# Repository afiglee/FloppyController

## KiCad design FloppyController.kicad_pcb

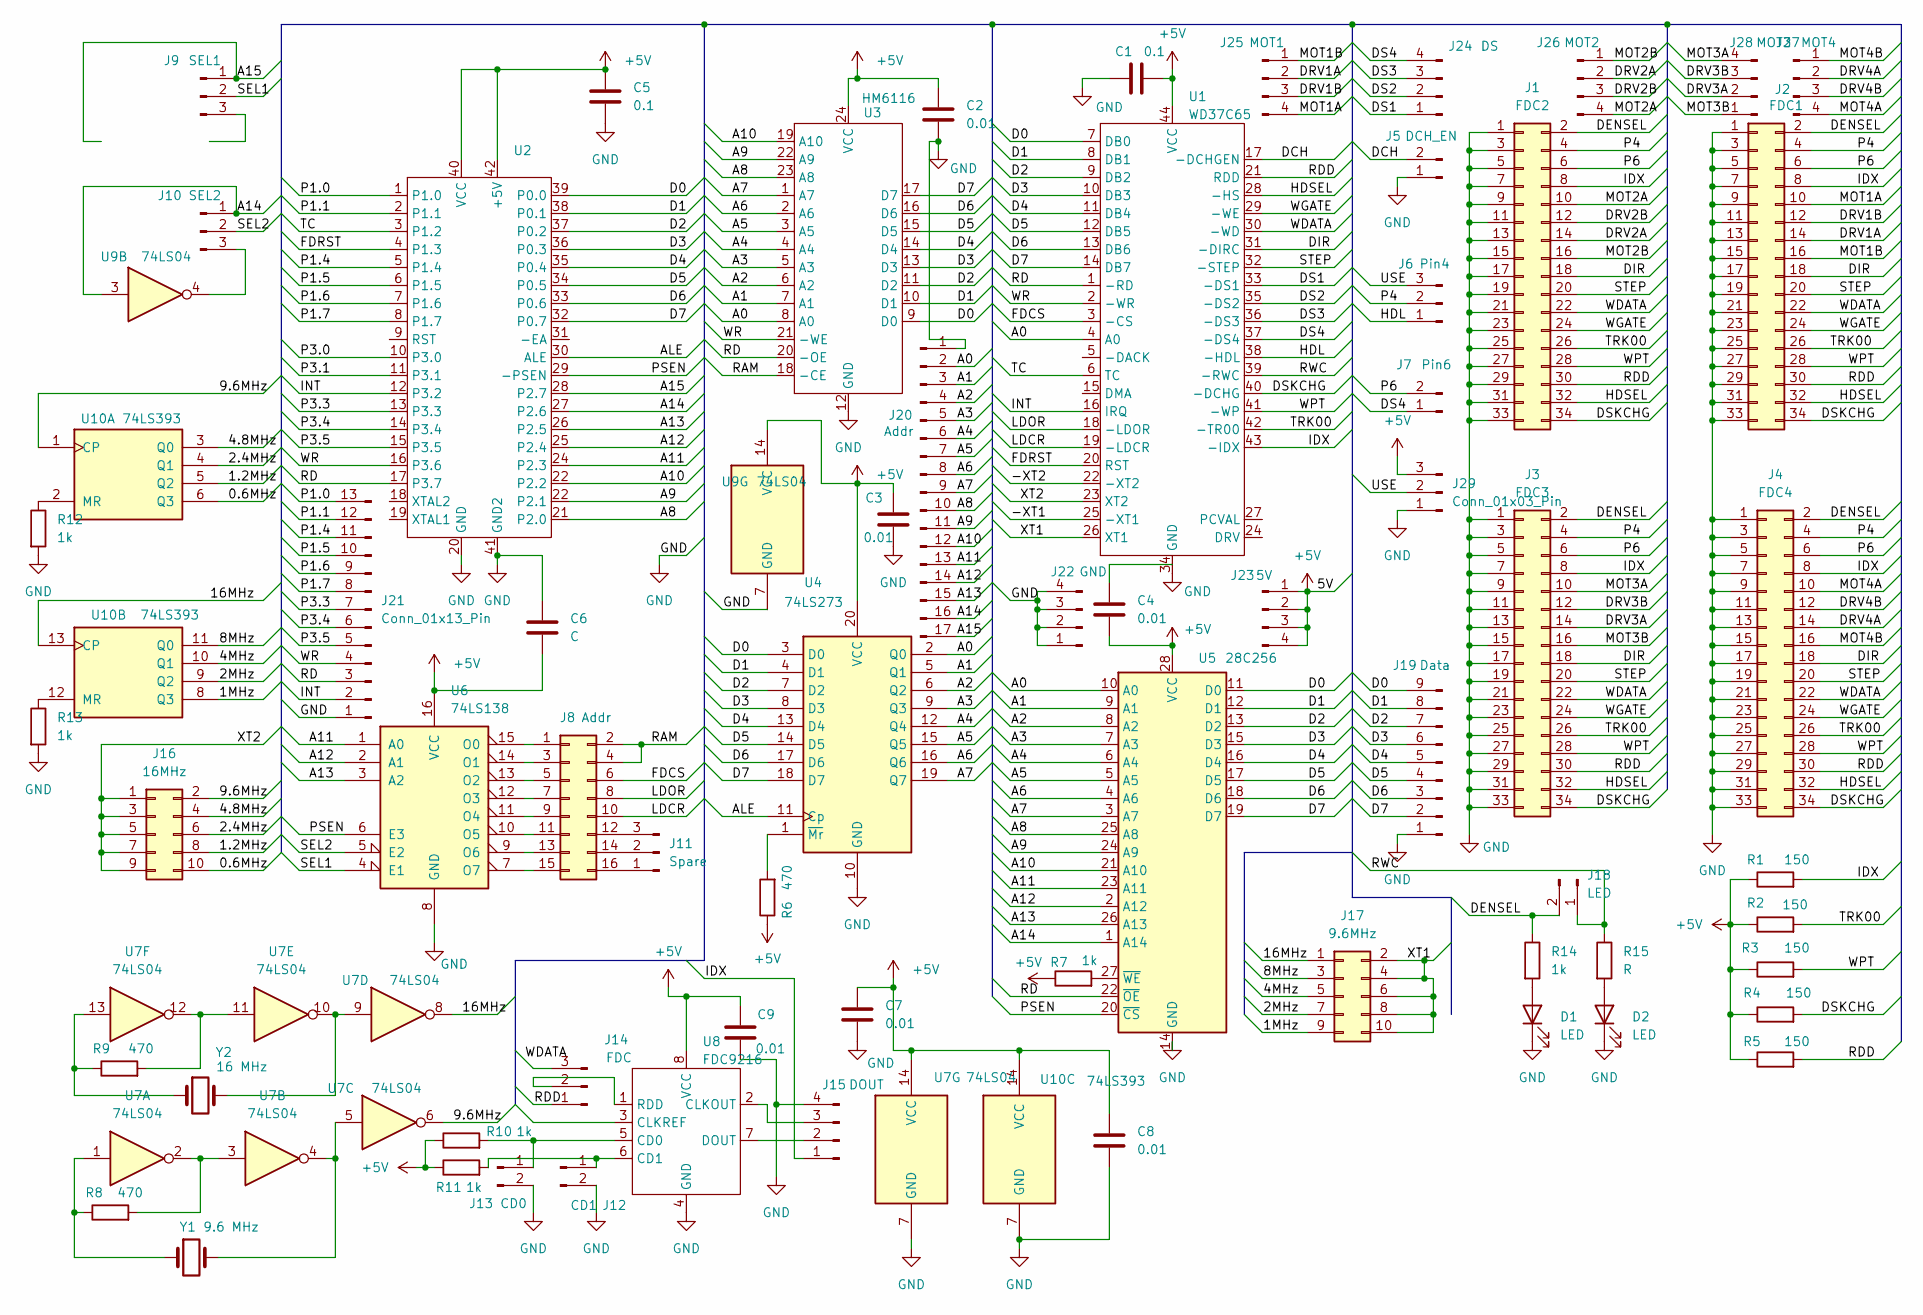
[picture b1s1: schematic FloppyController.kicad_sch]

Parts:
C1, C5: 0.1; C_Disc_D4.7mm_W2.5mm_P5.00mm
C2, C3, C4, C7, C8, C9: 0.01; C_Disc_D4.7mm_W2.5mm_P5.00mm
C6: C; C_Disc_D4.7mm_W2.5mm_P5.00mm
D1, D2: LED; LED_D5.0mm
J1: FDC2; PinHeader_2x17_P2.54mm_Vertical
J2: FDC1; PinHeader_2x17_P2.54mm_Vertical
J3: FDC3; PinHeader_2x17_P2.54mm_Vertical
J4: FDC4; PinHeader_2x17_P2.54mm_Vertical
J5: DCH_EN; PinHeader_1x02_P2.54mm_Vertical
J6: Pin4; PinHeader_1x03_P2.54mm_Vertical
J7: Pin6; PinHeader_1x02_P2.54mm_Vertical
J8: Addr; PinHeader_2x08_P2.54mm_Vertical
J9: SEL1; PinHeader_1x03_P2.54mm_Vertical
J10: SEL2; PinHeader_1x03_P2.54mm_Vertical
J11: Spare; PinHeader_1x03_P2.54mm_Vertical
J12: CD1; PinHeader_1x02_P2.54mm_Vertical
J13: CD0; PinHeader_1x02_P2.54mm_Vertical
J14: FDC; PinHeader_1x03_P2.54mm_Vertical
J15: DOUT; PinHeader_1x04_P2.54mm_Vertical
J16: 16MHz; PinHeader_2x05_P2.54mm_Vertical
J17: 9.6MHz; PinHeader_2x05_P2.54mm_Vertical
J18: LED; PinHeader_1x02_P2.54mm_Vertical
J19: Data; PinSocket_1x09_P2.54mm_Vertical
J20: Addr; PinHeader_1x17_P2.54mm_Vertical
J21: Conn_01x13_Pin; PinHeader_1x13_P2.54mm_Vertical
J22: GND; PinSocket_1x04_P2.54mm_Vertical
J23: 5V; PinSocket_1x04_P2.54mm_Vertical
J24: DS; PinHeader_1x04_P2.54mm_Vertical
J25: MOT1; PinHeader_1x04_P2.54mm_Vertical
J26: MOT2; PinHeader_1x04_P2.54mm_Vertical
J27: MOT4; PinHeader_1x04_P2.54mm_Vertical
J28: MOT3; PinHeader_1x04_P2.54mm_Vertical
J29: Conn_01x03_Pin; PinHeader_1x03_P2.54mm_Vertical
R1, R2, R3, R4, R5: 150; R_Axial_DIN0207_L6.3mm_D2.5mm_P10.16mm_Horizontal
R6, R8, R9: 470; R_Axial_DIN0207_L6.3mm_D2.5mm_P10.16mm_Horizontal
R7, R10, R11, R12, R13, R14: 1k; R_Axial_DIN0207_L6.3mm_D2.5mm_P10.16mm_Horizontal
R15: R; R_Axial_DIN0207_L6.3mm_D2.5mm_P10.16mm_Horizontal
U1: WD37C65; PLCC-44_THT-Socket
U2: 8051break
U3: HM6116; DIP-24_W15.24mm_Socket_LongPads
U4: 74LS273; DIP-20_W7.62mm_Socket_LongPads
U5: 28C256; DIP-28_W15.24mm_Socket_LongPads
U6: 74LS138; DIP-16_W7.62mm_Socket_LongPads
U7, U9: 74LS04; DIP-14_W7.62mm_Socket_LongPads
U8: FDC9216; DIP-8_W7.62mm_Socket_LongPads
U10: 74LS393; DIP-14_W7.62mm_Socket_LongPads
Y1: 9.6 MHz; Crystal_HC49-U_Vertical
Y2: 16 MHz; Crystal_HC49-U_Vertical

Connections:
+5V: C1.2, C2.1, C3.1, C4.2, C5.1, C6.2, C7.1, C8.1, C9.1, J23.1, J23.2, J23.3, J23.4, J29.3, R1.1, R2.1, R3.1, R4.1, R5.1, R6.1, R7.1, R10.1, R11.1, U1.44 (VCC), U2.40 (VCC), U2.42 (+5V), U3.24 (VCC), U4.20 (VCC), U5.28 (VCC), U6.16 (VCC), U7.14 (VCC), U8.8 (VCC), U9.14 (VCC), U10.14 (VCC)
/0.6MHz: J16.10, U10.6 (Q3)
/1.2MHz: J16.8, U10.5 (Q2)
/1MHz: J17.9, U10.8 (Q3)
/2.4MHz: J16.6, U10.4 (Q1)
/2MHz: J17.7, U10.9 (Q2)
/4.8MHz: J16.4, U10.3 (Q0)
/4MHz: J17.5, U10.10 (Q1)
/8MHz: J17.3, U10.11 (Q0)
/9.6MHz: J16.2, U7.6, U10.1 (CP)
/16MHz: J17.1, U7.8, U10.13 (CP)
/-XT1: U1.25 (-XT1)
/-XT2: U1.22 (-XT2)
/A0: J20.2, U1.4 (A0), U3.8 (A0), U4.2 (Q0), U5.10 (A0)
/A1: J20.3, U3.7 (A1), U4.5 (Q1), U5.9 (A1)
/A2: J20.4, U3.6 (A2), U4.6 (Q2), U5.8 (A2)
/A3: J20.5, U3.5 (A3), U4.9 (Q3), U5.7 (A3)
/A4: J20.6, U3.4 (A4), U4.12 (Q4), U5.6 (A4)
/A5: J20.7, U3.3 (A5), U4.15 (Q5), U5.5 (A5)
/A6: J20.8, U3.2 (A6), U4.16 (Q6), U5.4 (A6)
/A7: J20.9, U3.1 (A7), U4.19 (Q7), U5.3 (A7)
/A8: J20.10, U2.21 (P2.0), U3.23 (A8), U5.25 (A8)
/A11: J20.13, U2.24 (P2.3), U5.23 (A11), U6.1 (A0)
/A12: J20.14, U2.25 (P2.4), U5.2 (A12), U6.2 (A1)
/A13: J20.15, U2.26 (P2.5), U5.26 (A13), U6.3 (A2)
/A14: J10.1, J20.16, U2.27 (P2.6), U5.1 (A14), U9.3
/A15: J9.1, J20.17, U2.28 (P2.7)
/ALE: U2.30 (ALE), U4.11 (Cp)
/D0: J19.9, U1.7 (DB0), U2.39 (P0.0), U3.9 (D0), U4.3 (D0), U5.11 (D0)
/D1: J19.8, U1.8 (DB1), U2.38 (P0.1), U3.10 (D1), U4.4 (D1), U5.12 (D1)
/D2: J19.7, U1.9 (DB2), U2.37 (P0.2), U3.11 (D2), U4.7 (D2), U5.13 (D2)
/D3: J19.6, U1.10 (DB3), U2.36 (P0.3), U3.13 (D3), U4.8 (D3), U5.15 (D3)
/D4: J19.5, U1.11 (DB4), U2.35 (P0.4), U3.14 (D4), U4.13 (D4), U5.16 (D4)
/D5: J19.4, U1.12 (DB5), U2.34 (P0.5), U3.15 (D5), U4.14 (D5), U5.17 (D5)
/D6: J19.3, U1.13 (DB6), U2.33 (P0.6), U3.16 (D6), U4.17 (D6), U5.18 (D6)
/D7: J19.2, U1.14 (DB7), U2.32 (P0.7), U3.17 (D7), U4.18 (D7), U5.19 (D7)
/DCH: J5.2, U1.17 (-DCHGEN)
/DENSEL: J1.2, J2.2, J3.2, J4.2, J18.2, R14.1
/DIR: J1.18, J2.18, J3.18, J4.18, U1.31 (-DIRC)
/DRV1A: J2.14, J25.2
/DRV1B: J2.12, J25.3
/DRV2A: J1.14, J26.2
/DRV2B: J1.12, J26.3
/DRV3A: J3.14, J28.2
/DRV3B: J3.12, J28.3
/DRV4A: J4.14, J27.2
/DRV4B: J4.12, J27.3
/DS1: J24.1, U1.33 (-DS1)
/DS2: J24.2, U1.35 (-DS2)
/DS3: J24.3, U1.36 (-DS3)
/DS4: J7.1, J24.4, U1.37 (-DS4)
/DSKCHG: J1.34, J2.34, J3.34, J4.34, R4.2, U1.40 (-DCHG)
/FDCS: J8.6, U1.3 (-CS)
/FDRST: U1.20 (RST), U2.4 (P1.3)
/HDL: J6.1, U1.38 (-HDL)
/HDSEL: J1.32, J2.32, J3.32, J4.32, U1.28 (-HS)
/IDX: J1.8, J2.8, J3.8, J4.8, J15.1, R1.2, U1.43 (-IDX)
/INT: J21.2, U1.16 (IRQ), U2.12 (P3.2)
/LDCR: J8.10, U1.19 (-LDCR)
/LDOR: J8.8, U1.18 (-LDOR)
/MOT1A: J2.10, J25.4
/MOT1B: J2.16, J25.1
/MOT2A: J1.10, J26.4
/MOT2B: J1.16, J26.1
/MOT3A: J3.10, J28.4
/MOT3B: J3.16, J28.1
/MOT4A: J4.10, J27.4
/MOT4B: J4.16, J27.1
/P1.0: J21.13, U2.1 (P1.0)
/P1.1: J21.12, U2.2 (P1.1)
/P1.4: J21.11, U2.5 (P1.4)
/P1.5: J21.10, U2.6 (P1.5)
/P1.6: J21.9, U2.7 (P1.6)
/P1.7: J21.8, U2.8 (P1.7)
/P3.0: U2.10 (P3.0)
/P3.1: U2.11 (P3.1)
/P3.3: J21.7, U2.13 (P3.3)
/P3.4: J21.6, U2.14 (P3.4)
/P3.5: J21.5, U2.15 (P3.5)
/P4: J1.4, J2.4, J3.4, J4.4, J6.2
/P6: J1.6, J2.6, J3.6, J4.6, J7.2
/PSEN: U2.29 (-PSEN), U5.20 (~CS), U6.6 (E3)
/RAM: J8.2, J8.4, U3.18 (-CE)
/RD: J21.3, U1.1 (-RD), U2.17 (P3.7), U3.20 (-OE), U5.22 (~OE)
/RDD: J1.30, J2.30, J3.30, J4.30, J14.1, R5.2, U1.21 (RDD)
/RWC: J18.1, R15.1, U1.39 (-RWC)
/SEL1: J9.2, U6.4 (E1)
/SEL2: J10.2, U6.5 (E2)
/STEP: J1.20, J2.20, J3.20, J4.20, U1.32 (-STEP)
/TC: U1.6 (TC), U2.3 (P1.2)
/TRK00: J1.26, J2.26, J3.26, J4.26, R2.2, U1.42 (-TR00)
/USE: J6.3, J29.2
/WDATA: J1.22, J2.22, J3.22, J4.22, U1.30 (-WD)
/WGATE: J1.24, J2.24, J3.24, J4.24, U1.29 (-WE)
/WPT: J1.28, J2.28, J3.28, J4.28, R3.2, U1.41 (-WP)
/WR: J21.4, U1.2 (-WR), U2.16 (P3.6), U3.21 (-WE)
/XT1: J17.2, J17.4, J17.6, J17.8, J17.10, U1.26 (XT1)
/XT2: J16.1, J16.3, J16.5, J16.7, J16.9, U1.23 (XT2)
GND: C1.1, C2.2, C3.2, C5.2, C6.1, C7.2, C8.2, C9.2, D1.1 (K), D2.1 (K), J1.1, J1.3, J1.5, J1.7, J1.9, J1.11, J1.13, J1.15, J1.17, J1.19, J1.21, J1.23, J1.25, J1.27, J1.29, J1.31, J1.33, J2.1, J2.3, J2.5, J2.7, J2.9, J2.11, J2.13, J2.15, J2.17, J2.19, J2.21, J2.23, J2.25, J2.27, J2.29, J2.31, J2.33, J3.1, J3.3, J3.5, J3.7, J3.9, J3.11, J3.13, J3.15, J3.17, J3.19, J3.21, J3.23, J3.25, J3.27, J3.29, J3.31, J3.33, J4.1, J4.3, J4.5, J4.7, J4.9, J4.11, J4.13, J4.15, J4.17, J4.19, J4.21, J4.23, J4.25, J4.27, J4.29, J4.31, J4.33, J5.1, J12.2, J13.2, J15.4, J19.1, J20.1, J21.1, J22.1, J22.2, J22.3, J22.4, J29.1, R12.2, R13.2, U1.34 (GND), U2.20 (GND), U2.41 (GND2), U3.12 (GND), U4.10 (GND), U5.14 (GND), U6.8 (GND), U7.7 (GND), U8.4 (GND), U9.7 (GND), U10.7 (GND)
unnamed: D1.2 (A), R14.2
unnamed: D2.2 (A), R15.2
unnamed: J8.1, U6.15 (O0)
unnamed: J8.3, U6.14 (O1)
unnamed: J8.5, U6.13 (O2)
unnamed: J8.7, U6.12 (O3)
unnamed: J8.9, U6.11 (O4)
unnamed: J8.11, U6.10 (O5)
unnamed: J8.13, U6.9 (O6)
unnamed: J8.15, U6.7 (O7)
unnamed: J10.3, U9.4
unnamed: J8.16, J11.1
unnamed: J8.14, J11.2
unnamed: J8.12, J11.3
unnamed: J12.1, R11.2, U8.6 (CD1)
unnamed: J13.1, R10.2, U8.5 (CD0)
unnamed: J14.2, U8.1 (RDD)
unnamed: J15.2, U8.7 (DOUT)
unnamed: J15.3, U8.2 (CLKOUT)
unnamed: R8.1, U7.1, Y1.1
unnamed: R8.2, U7.2, U7.3
unnamed: R9.1, U7.13, Y2.1
unnamed: R9.2, U7.11, U7.12
unnamed: R6.2, U4.1 (~Mr)
unnamed: R7.2, U5.27 (~WE)
unnamed: U7.4, U7.5, Y1.2
unnamed: U7.9, U7.10, Y2.2
unnamed: R12.1, U10.2 (MR)
unnamed: R13.1, U10.12 (MR)

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
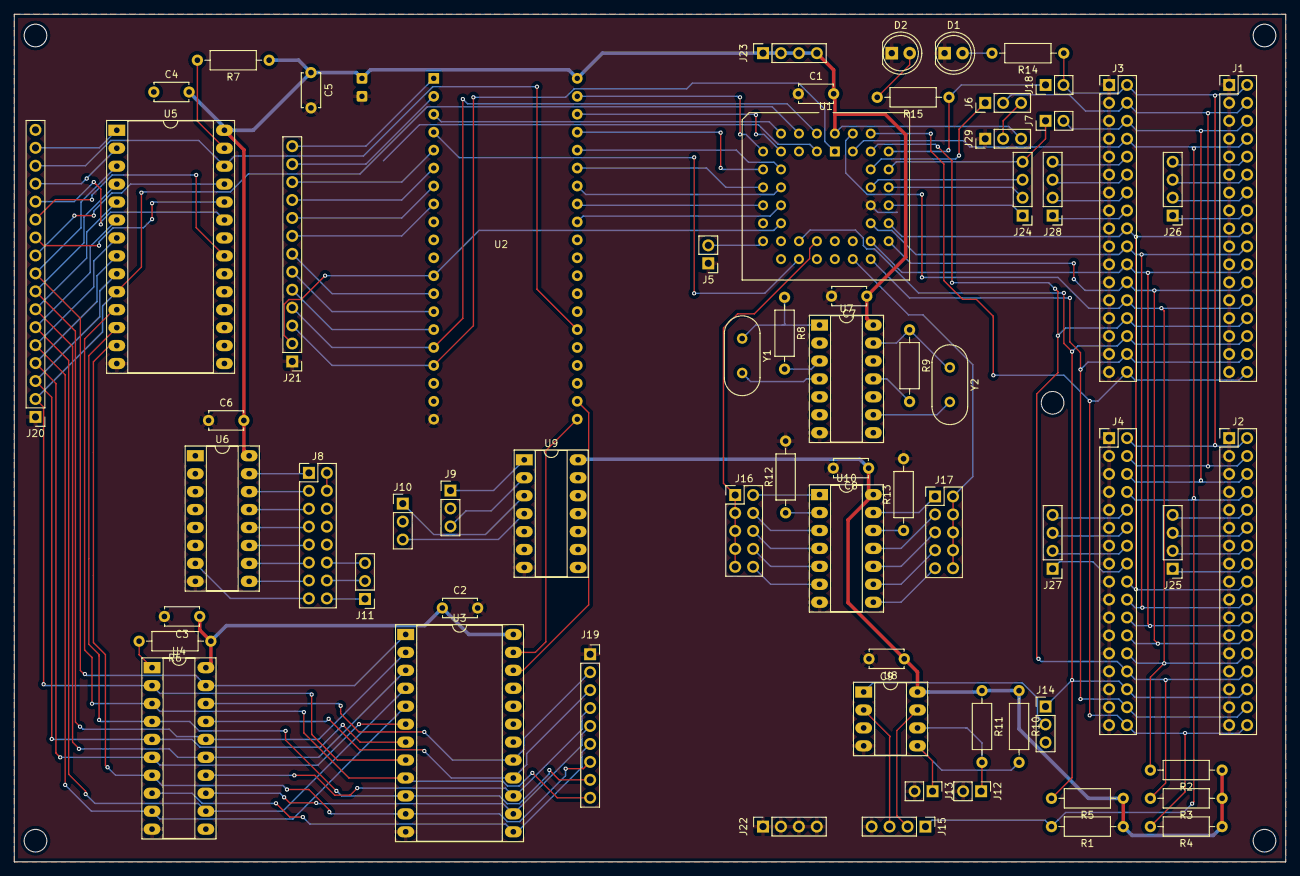
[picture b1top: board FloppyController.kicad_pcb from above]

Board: 2 copper layers, 180.0 x 120.0 mm, 67 parts (0 on the bottom side), 126 nets.

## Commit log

2024-07-29 Work in progress
